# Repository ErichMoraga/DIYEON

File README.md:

# DIYEON

This ia A DIY EON with Magnetic Mount

What you need

2  *   40x40x7mm7mm 5v fan

1  *    150mm x 60mm x 5mm aluminium heat sink

1  *   Thermal Paste

2  *   Pololu USB 2.0 Type-C Connector Breakout Board

6  *   3mm Screws

6  *   3mm Inserts

1  *   USB Type C Cable, 180 Degree Right Angle

16 *  Neodymium magnet 6mm OD 3mm Thick

1  *  Glue

1  * 10P Probe Connector Spring Thimble Charging Spring Needle Conductive Connector Electronic Shock M885/10P

Soldering iron (soldering flux makes soldering so much easier :) )

Note:

Parts could be found on Amazon, ebay and robotshop
Pic of Finished Project will be added soon

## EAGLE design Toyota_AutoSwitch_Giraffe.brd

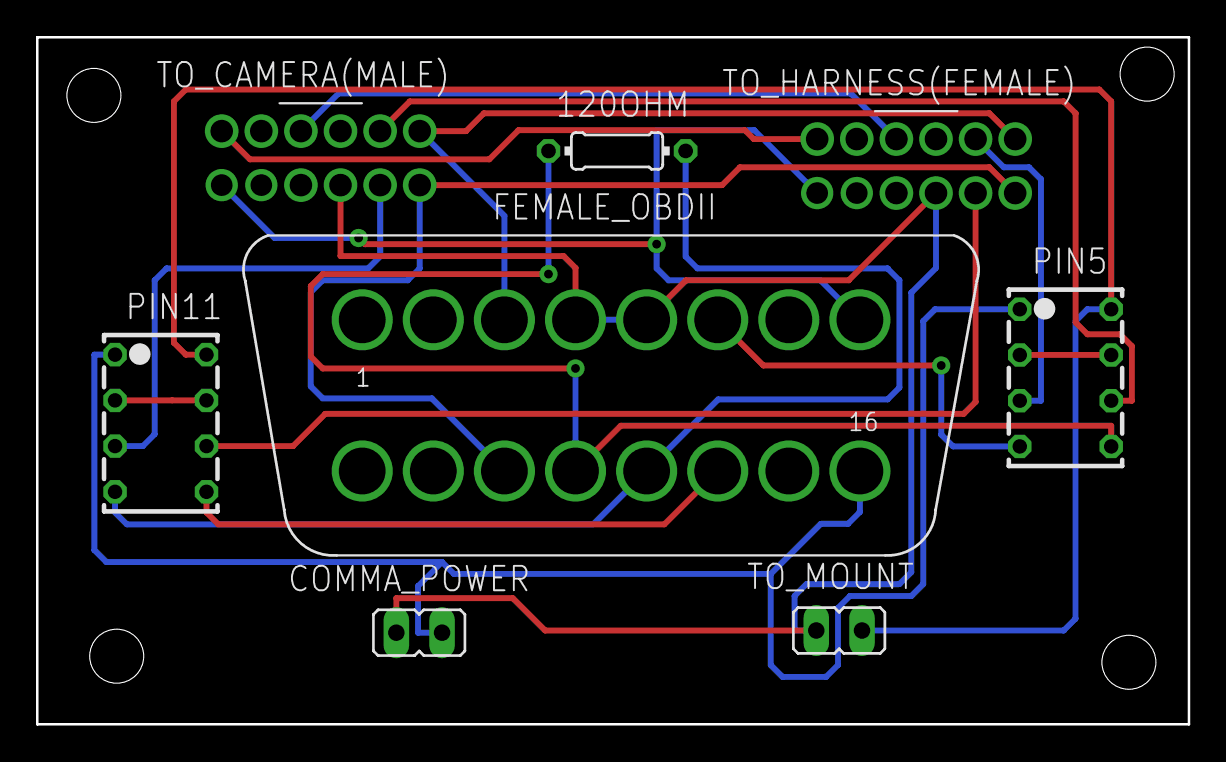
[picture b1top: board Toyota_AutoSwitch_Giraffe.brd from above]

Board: 2 copper layers, 64.0 x 38.2 mm, 8 parts (0 on the bottom side), 18 nets.

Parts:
120OHM: R-US_0204/7 (R-US_); 0204/7
COMMA_POWER: JP1E; JP1
FEMALE_OBDII: OBDIIFEMALE (OBDII); OBDII-FEMALE
PIN5, PIN11: G6K-2P (G6K); G6K-2P
TO_CAMERA(MALE): MOBILEEYE-12FEMALE (MOBILEEYE-12); 2X6-TE-FEMALE
TO_HARNESS(FEMALE): MOBILEEYE-12FEMALE (MOBILEEYE-12); 2X6-TE-FEMALE
TO_MOUNT: JP1E; JP1

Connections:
unnamed: TO_CAMERA(MALE).1, TO_HARNESS(FEMALE).1
unnamed: TO_CAMERA(MALE).3, TO_HARNESS(FEMALE).3
unnamed: PIN5.6, TO_CAMERA(MALE).5
unnamed: COMMA_POWER.2, FEMALE_OBDII.4, FEMALE_OBDII.5, TO_CAMERA(MALE).10, TO_HARNESS(FEMALE).10, TO_MOUNT.2
unnamed: 120OHM.1, FEMALE_OBDII.12, PIN5.5
unnamed: 120OHM.2, FEMALE_OBDII.13, PIN11.4
unnamed: PIN5.2, PIN5.7
unnamed: FEMALE_OBDII.11, TO_CAMERA(MALE).12, TO_HARNESS(FEMALE).12
unnamed: FEMALE_OBDII.3, TO_CAMERA(MALE).6, TO_HARNESS(FEMALE).6
unnamed: FEMALE_OBDII.8, TO_CAMERA(MALE).7, TO_HARNESS(FEMALE).7
unnamed: PIN11.3, TO_CAMERA(MALE).11
unnamed: FEMALE_OBDII.6, PIN5.4
unnamed: COMMA_POWER.1, FEMALE_OBDII.16, PIN5.1, PIN11.1
unnamed: PIN11.6, TO_HARNESS(FEMALE).11
unnamed: PIN5.8, PIN11.8, TO_MOUNT.1
unnamed: PIN11.2, PIN11.7
unnamed: PIN5.3, TO_HARNESS(FEMALE).5
unnamed: FEMALE_OBDII.14, PIN11.5

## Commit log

2019-11-03 Add files via upload
    Reduce internal clearance by 0.30mm for better fit
2019-11-03 Create BOM.csv
    Trying to get the ball rolling, curious what exactly @gandalffoogray used.
